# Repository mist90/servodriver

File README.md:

# servodriver
Scheme and firmware for 3-phase servomotor controller

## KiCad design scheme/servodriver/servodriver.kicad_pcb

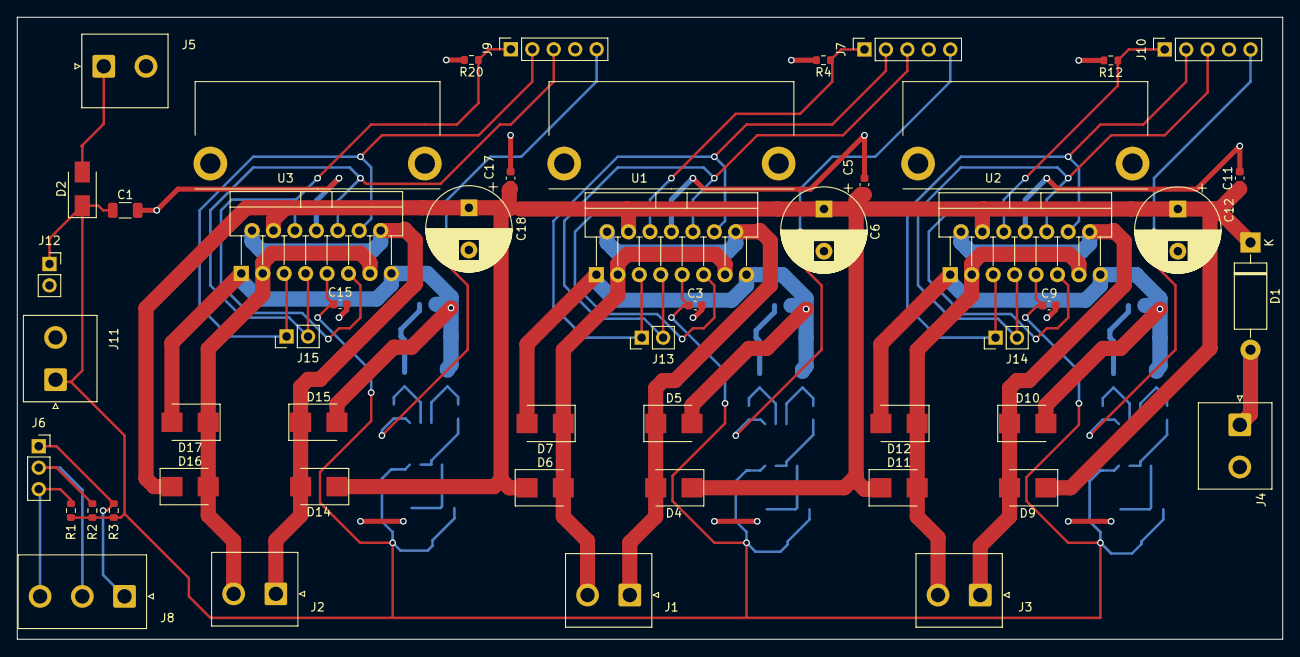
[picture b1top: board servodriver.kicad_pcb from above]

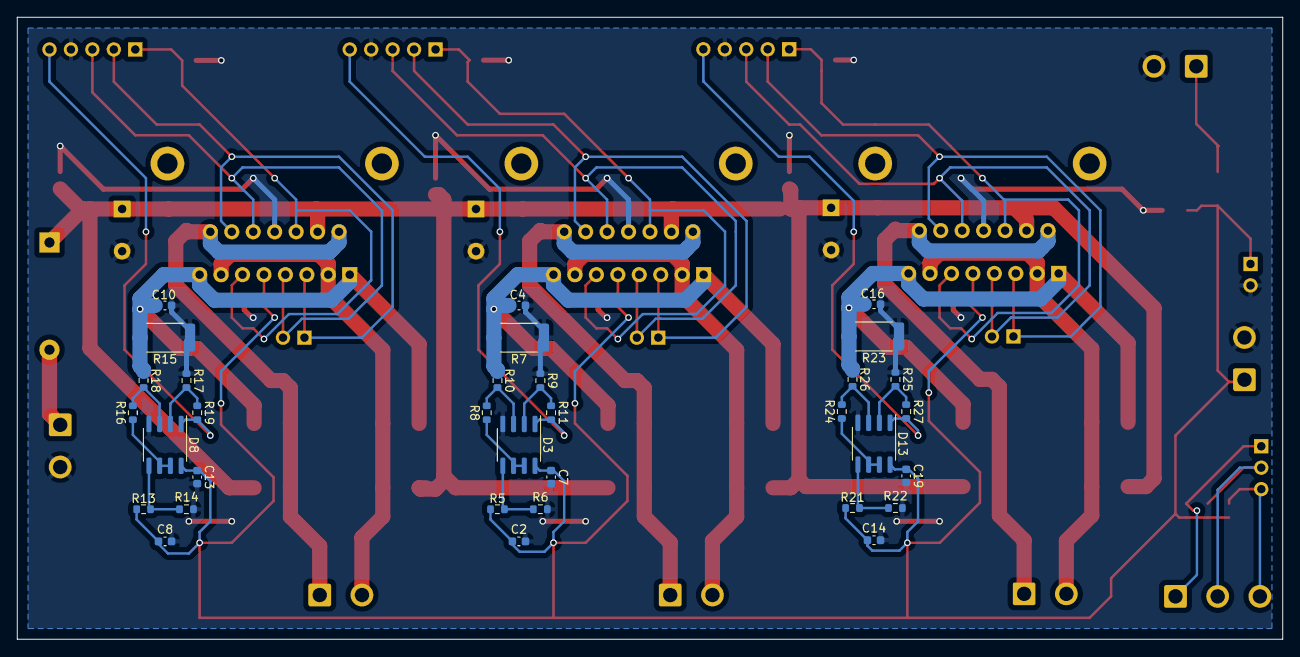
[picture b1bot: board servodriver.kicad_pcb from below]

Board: 2 copper layers, 149.9 x 73.7 mm, 81 parts (33 on the bottom side), 41 nets.

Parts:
C1: 10 мкФ 25В; C_1206_3216Metric
C2, C3, C5, C7, C8, C9, C11, C13, C14, C15, C17, C19: 0.1мкФ 50В; C_0603_1608Metric
C4, C10, C16: 1000 пФ 50В; C_0603_1608Metric
C6, C12, C18: К50-35 330мкФ 50В; CP_Radial_D10.0mm_P5.00mm
D1: 15SQ045; D_DO-15_P12.70mm_Horizontal
D2: 10MQ40; D_SMA
D3, D8, D13: AD8602; SOIC-8_3.9x4.9mm_P1.27mm
D4, D5, D6, D7, D9, D10, D11, D12, D14, D15, D16, D17: SS510B; D_SMB
J1, J2, J3, J4, J5, J11: KLS2-102-5.00-02P-2S; JST_NV_B02P-NV_1x02_P5.00mm_Vertical
J6: PLS-3; PinSocket_1x03_P2.54mm_Vertical
J7, J9, J10: PLS-5; PinSocket_1x05_P2.54mm_Vertical
J8: KLS2-128I-5.00-03P-4S; JST_NV_B03P-NV_1x03_P5.00mm_Vertical
J12: PLS-2; PinSocket_1x02_P2.54mm_Vertical
J13, J14, J15: PLS-2; PinHeader_1x02_P2.54mm_Vertical
R1, R2, R3, R4, R5, R12, R13, R20, R21: 10 кОм 5%; R_0603_1608Metric
R6, R14, R22: 5 кОм 5%; R_0603_1608Metric
R7, R15, R23: 0.047 Ом 1%; R_2512_6332Metric
R8, R11, R16, R19, R24, R27: 10 кОм 1%; R_0603_1608Metric
R9, R10, R17, R18, R25, R26: 1 кОм 1%; R_0603_1608Metric
U1, U2, U3: L298HN; TO-220-15_P2.54x2.54mm_StaggerOdd_Lead4.58mm_Vertical

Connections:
+5V: C1.1, C2.1, C3.1, C7.1, C8.1, C9.1, C13.1, C14.1, C15.1, C19.1, D2.1 (K), D3.8 (V+), D8.8 (V+), D13.8 (V+), J11.1, J12.1, R1.1, R2.1, R3.1, R5.1, R13.1, R21.1, U1.9 (Vss), U2.9 (Vss), U3.9 (Vss)
+36V: C5.1, C6.1, C11.1, C12.1, C17.1, C18.1, D1.1 (K), D4.1 (K), D6.1 (K), D9.1 (K), D11.1 (K), D14.1 (K), D16.1 (K), U1.4 (Vs), U2.4 (Vs), U3.4 (Vs)
/En1: J7.1, R4.1, U1.6 (EnA), U1.11 (EnB)
/En2: J9.1, R20.1, U3.6 (EnA), U3.11 (EnB)
/En3: J10.1, R12.1, U2.6 (EnA), U2.11 (EnB)
/Half-Bridge1/SenseGND: C10.2, D10.2 (A), D12.2 (A), R15.1, R18.1, U2.1 (SENSE_A), U2.15 (SENSE_B)
/Half-Bridge2/SenseGND: C16.2, D15.2 (A), D17.2 (A), R23.1, R26.1, U3.1 (SENSE_A), U3.15 (SENSE_B)
/Half-Bridge/SenseGND: C4.2, D5.2 (A), D7.2 (A), R7.1, R10.1, U1.1 (SENSE_A), U1.15 (SENSE_B)
/In1_1: J7.2, J13.1, U1.5 (IN1), U1.12 (IN4)
/In1_2: J7.3, J13.2, U1.7 (IN2), U1.10 (IN3)
/In2_1: J9.2, J15.1, U3.5 (IN1), U3.12 (IN4)
/In2_2: J9.3, J15.2, U3.7 (IN2), U3.10 (IN3)
/In3_1: J10.2, J14.1, U2.5 (IN1), U2.12 (IN4)
/In3_2: J10.3, J14.2, U2.7 (IN2), U2.10 (IN3)
/Out1_1: D4.2 (A), D5.1 (K), J1.1, U1.2 (OUT1), U1.14 (OUT4)
/Out1_2: D6.2 (A), D7.1 (K), J1.2, U1.3 (OUT2), U1.13 (OUT3)
/Out2_1: D14.2 (A), D15.1 (K), J2.1, U3.2 (OUT1), U3.14 (OUT4)
/Out2_2: D16.2 (A), D17.1 (K), J2.2, U3.3 (OUT2), U3.13 (OUT3)
/Out3_1: D9.2 (A), D10.1 (K), J3.1, U2.2 (OUT1), U2.14 (OUT4)
/Out3_2: D11.2 (A), D12.1 (K), J3.2, U2.3 (OUT2), U2.13 (OUT3)
/Sense1: D3.1 (OUTa), J7.5, R11.2
/Sense2: D13.1 (OUTa), J9.5, R27.2
/Sense3: D8.1 (OUTa), J10.5, R19.2
GND: C1.2, C2.2, C3.2, C4.1, C5.2, C6.2, C7.2, C8.2, C9.2, C10.1, C11.2, C12.2, C13.2, C14.2, C15.2, C16.1, C17.2, C18.2, C19.2, D3.4 (V-), D8.4 (V-), D13.4 (V-), J4.2, J5.2, J7.4, J9.4, J10.4, J11.2, J12.2, R4.2, R6.2, R7.2, R9.1, R12.2, R14.2, R15.2, R17.1, R20.2, R22.2, R23.2, R25.1, U1.8 (GND), U2.8 (GND), U3.8 (GND)
unnamed: D1.2 (A), J4.1
unnamed: D2.2 (A), J5.1
unnamed: D3.2 (-INa), R9.2, R11.1
unnamed: D3.3 (+INa), R8.2, R10.2
unnamed: D3.5 (+INb), R5.2, R6.1
unnamed: D3.6 (-INb), D3.7 (OUTb), R8.1
unnamed: D8.2 (-INa), R17.2, R19.1
unnamed: D8.3 (+INa), R16.2, R18.2
unnamed: D8.5 (+INb), R13.2, R14.1
unnamed: D8.6 (-INb), D8.7 (OUTb), R16.1
unnamed: D13.2 (-INa), R25.2, R27.1
unnamed: D13.3 (+INa), R24.2, R26.2
unnamed: D13.5 (+INb), R21.2, R22.1
unnamed: D13.6 (-INb), D13.7 (OUTb), R24.1
unnamed: J6.1, J8.1, R3.2
unnamed: J6.2, J8.2, R2.2
unnamed: J6.3, J8.3, R1.2

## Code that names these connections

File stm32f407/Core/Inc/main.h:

/* USER CODE BEGIN Header */
/**
  ******************************************************************************
  * @file           : main.h
  * @brief          : Header for main.c file.
  *                   This file contains the common defines of the application.
  ******************************************************************************
  * @attention
  *
  * Copyright (c) 2024 STMicroelectronics.
  * All rights reserved.
  *
  * This software is licensed under terms that can be found in the LICENSE file
  * in the root directory of this software component.
  * If no LICENSE file comes with this software, it is provided AS-IS.
  *
  ******************************************************************************
  */
/* USER CODE END Header */

/* Define to prevent recursive inclusion -------------------------------------*/
#ifndef __MAIN_H
#define __MAIN_H

#ifdef __cplusplus
extern "C" {
#endif

/* Includes ------------------------------------------------------------------*/
#include "stm32f4xx_hal.h"

/* Private includes ----------------------------------------------------------*/
/* USER CODE BEGIN Includes */

/* USER CODE END Includes */

/* Exported types ------------------------------------------------------------*/
/* USER CODE BEGIN ET */

/* USER CODE END ET */

/* Exported constants --------------------------------------------------------*/
/* USER CODE BEGIN EC */

/* USER CODE END EC */

/* Exported macro ------------------------------------------------------------*/
/* USER CODE BEGIN EM */

/* USER CODE END EM */

void HAL_TIM_MspPostInit(TIM_HandleTypeDef *htim);

/* Exported functions prototypes ---------------------------------------------*/
void Error_Handler(void);

/* USER CODE BEGIN EFP */

/* USER CODE END EFP */

/* Private defines -----------------------------------------------------------*/
#define Sense1_Pin GPIO_PIN_0
#define Sense1_GPIO_Port GPIOA
#define Sense2_Pin GPIO_PIN_1
#define Sense2_GPIO_Port GPIOA
#define Sense3_Pin GPIO_PIN_2
#define Sense3_GPIO_Port GPIOA
#define In1_1_Pin GPIO_PIN_10
#define In1_1_GPIO_Port GPIOE
#define In2_1_Pin GPIO_PIN_12
#define In2_1_GPIO_Port GPIOE
#define In3_1_Pin GPIO_PIN_14
#define In3_1_GPIO_Port GPIOE
#define En3_Pin GPIO_PIN_10
#define En3_GPIO_Port GPIOB
#define En1_Pin GPIO_PIN_15
#define En1_GPIO_Port GPIOA
#define En2_Pin GPIO_PIN_3
#define En2_GPIO_Port GPIOB

/* USER CODE BEGIN Private defines */

/* USER CODE END Private defines */

#ifdef __cplusplus
}
#endif

#endif /* __MAIN_H */

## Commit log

2024-07-20 STM32: C++ code is moved to servo.* files
2024-07-21 STM32: PWM Timer control is changed
2024-07-22 - STM32: refactoring - gitignore is fixed
2024-07-24 новый файл: connections.ods
2024-07-30 Enable IRQ for PWM current control
2024-08-02 PWM current control is made
2024-08-04 Current control debugging
2024-08-10 STM32: current control debugging
2024-08-11 debug printf is added
2024-08-12 STM32F407 project is added
2024-08-12 STM32F407: project is ported from STM32F410
2024-08-13 STM32F407: current control is added
2024-08-13 изменено: .gitignore
2024-08-15 STM32F407: current control debugging
2024-08-18 STM32F407: current control debug
2024-08-20 изменено: connections.ods
